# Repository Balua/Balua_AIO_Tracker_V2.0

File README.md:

### Balua_AIO_Tracker_V2.0 - Board finished for printing, schematic and layout completed but still to be tested...

#### Updated version of the original tracker found in the Balua_AIO_Tracker_V1.0 repository with extra features and small corrections

#### Features:

#####Microprocessor
- ATMEGA 328p smd package

#####Power
- Step up Boost Converters from 2 AA Batteries to 3.3V and 5V

#####Communication
- Radiometrix HX1 - VHF Narrow Band FM High Power (300mW) Transmitter with SMA Antenna
- RFM22B ISM Transceiver Module with SMA Antenna

#####GPS
- Ublox Max 7 GPS with Quad V GPS antenna with jumpers in the RX/TX line and in the I2C for hardware selectable communication mode (NEW!!!)

#####Sensors
- SMD Onewire temperature sensor - DS18B20
- Battery Voltage sensing
- 0-15psi Pressure Sensor SMT mount - HSCSANN015PA2A3
- 9-axis Motion Tracking MEMS (3-axis gyroscope, 3-axis accelerometer and magnetometer) - MPU-9150 (NEW!!!)

#####Storage
- MicroSD Socket

#####Programming
- SMD AVR SPI Programming pins available (NEW!!!)

#####External pins
- I2c Pins with pull-up for expansion available
- 2 pins for Software Serial
- 2 pins for Hardware Serial
- Power Pins for external power (VBatt, 5V, 3.3V and GND) (NEW!!!)
- Power pins for Cutoff system (NEW!!!)

#####Other
- On Board AA battery holder
- 5V boost converter with enable controllable
- UBlox GPS Power ON Controllable
- RFM22B Radio enable pin Controllable
- On board LED
- Cutoff System implemented (NEW!!!)

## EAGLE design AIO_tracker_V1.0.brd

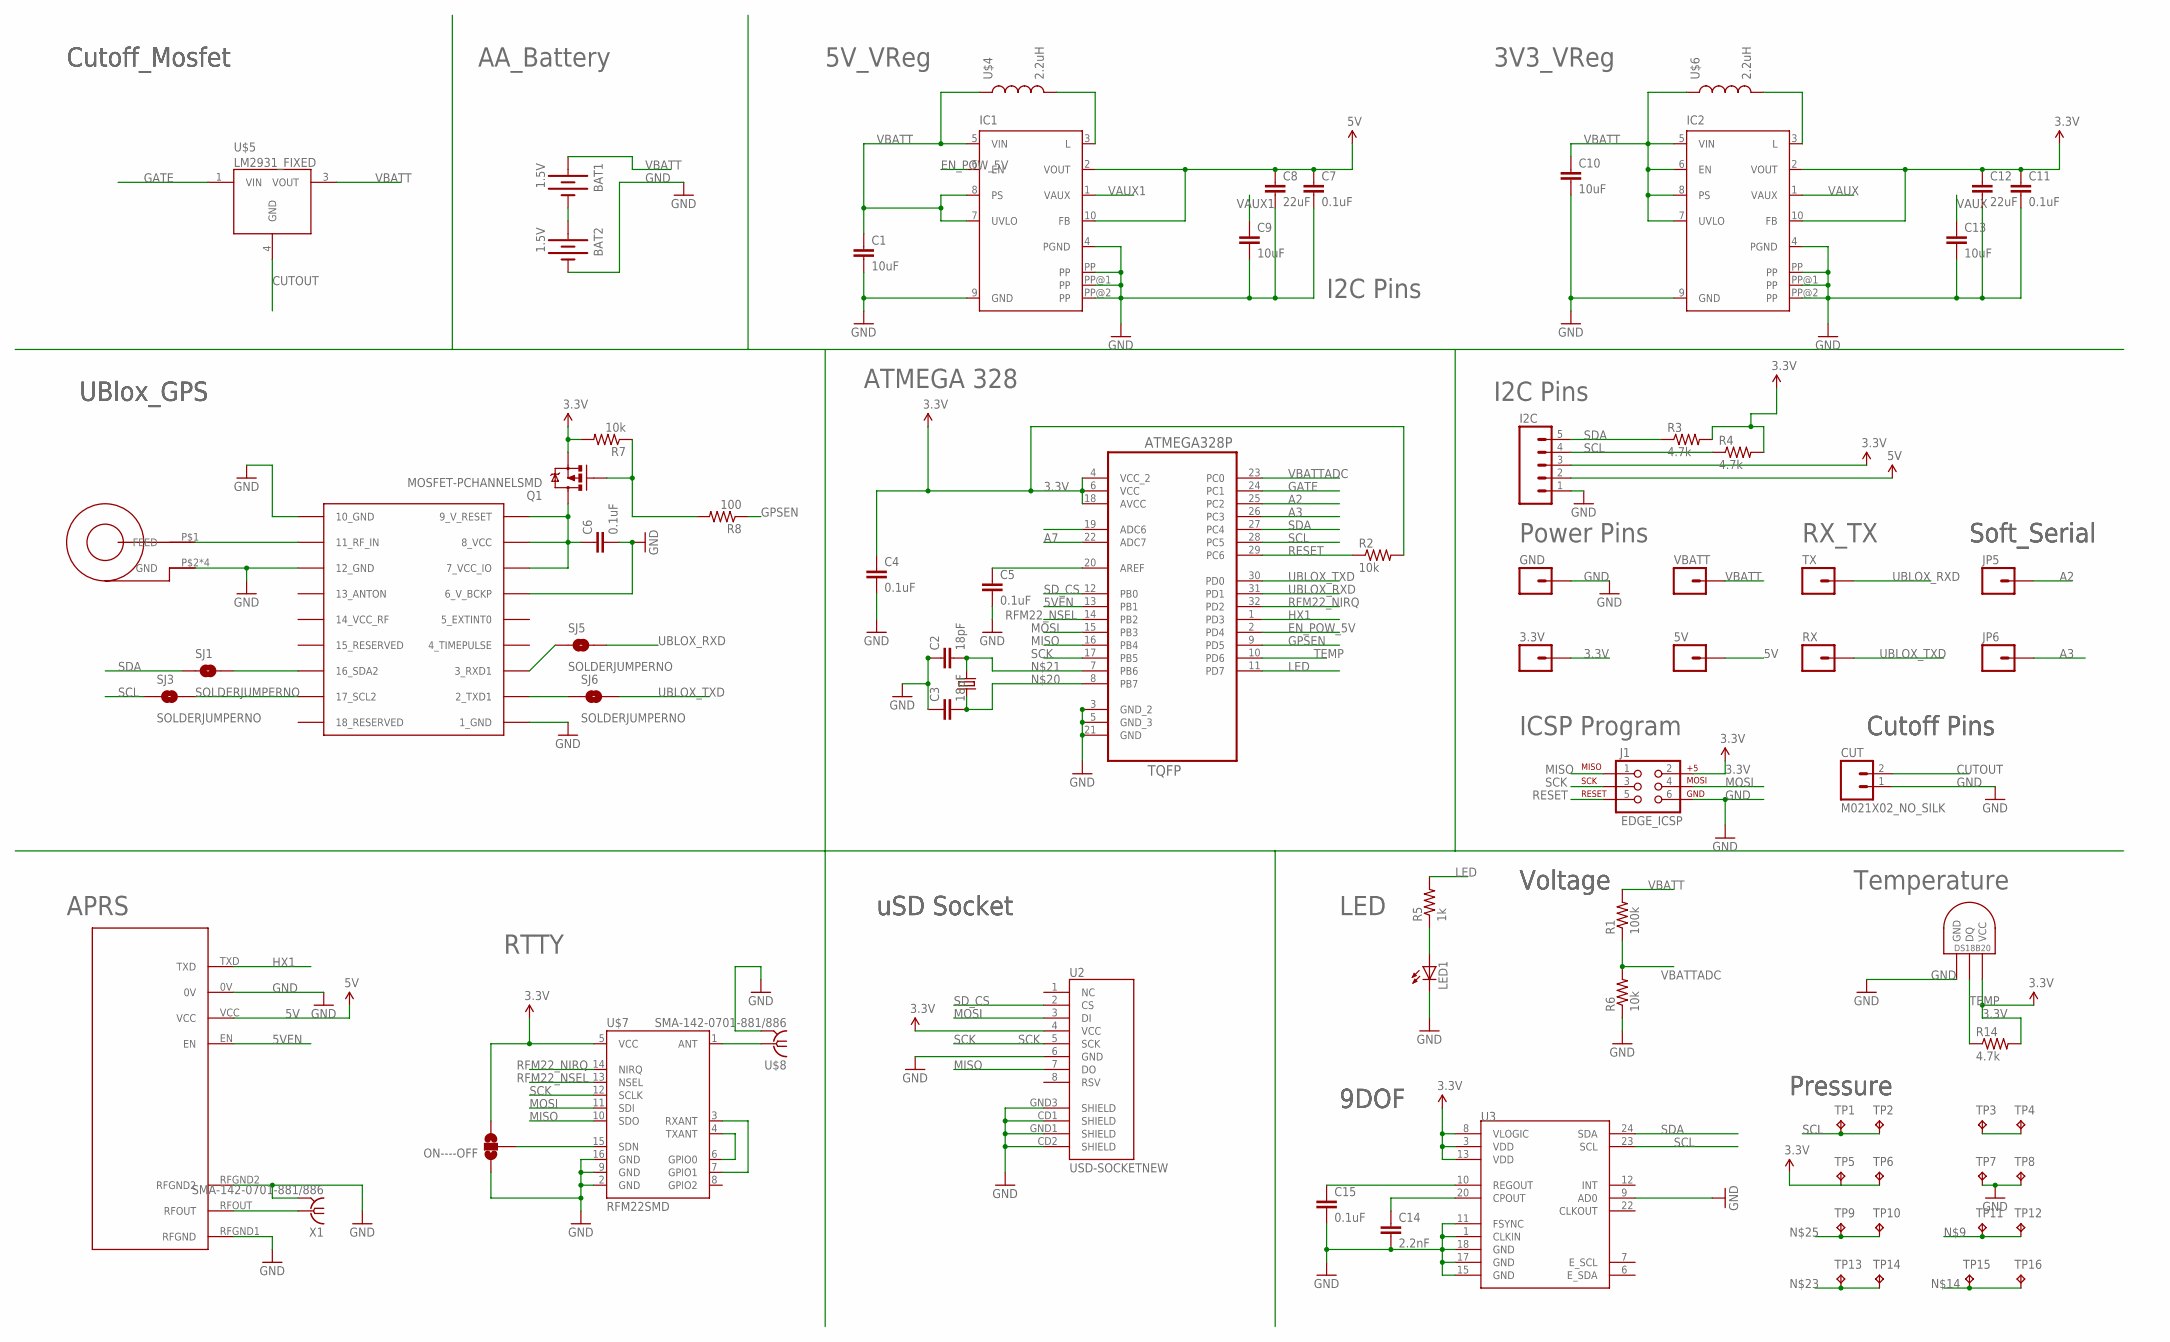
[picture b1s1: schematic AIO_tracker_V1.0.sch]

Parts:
3.3V, 5V: M01SMDNS; 1X01NS
BAT1, BAT2: 1.5V; BATTERY-AA-KIT
C1, C9, C10, C13: 10uF; 0805
C2, C3: 18pF; 0603-CAP
C4, C5, C6, C7, C11, C15: 0.1uF; 0603-CAP
C8, C12: 22uF; 0805
C14: 2.2nF; 0603-CAP
CUT: M021X02_NO_SILK; 1X02_NO_SILK
GND: M01SMDNS; 1X01NS
I2C: M05NO_SILK; 1X05_NO_SILK
IC1, IC2: TPS61201; S-PDSO-N10
J1: EDGE_ICSP; EDGE_MOUNTED_ICSP
JP5, JP6: M01PTH; 1X01
LED1: LED0603; LED-0603
ON----OFF: SOLDERJUMPER_2WAY-OLDT; SJ_2
Q1: MOSFET-PCHANNELSMD; SOT23-3
R1: 100k; 0603-RES
R2, R6, R7: 10k; 0603-RES
R3, R4, R14: 4.7k; 0603-RES
R5: 1k; 0603-RES
R8: 100; 0603-RES
RX: M01PTH; 1X01
SJ1, SJ3, SJ5, SJ6: SOLDERJUMPERNO; SJ_2S-NO
TP1, TP2, TP3, TP4, TP5, TP6, TP7, TP8, TP9, TP10, TP11, TP12, TP13, TP14, TP15, TP16: TPTP10SQ; TP10SQ
TX: M01PTH; 1X01
U1: ATMEGA328P-AU; QFP80P900X900X120-32N
U2: USD-SOCKETNEW; MICRO-SD-SOCKET-PP
U3: MPU-9150QFN-24-NP; QFN-24-NP
U$1: UBLOX_MAX
U$2: JDGA-REMQV-ANTENNA; JDGA-RIGID_COMBO_PAD
U$3: NTX2-VERTICAL
U$4, U$6: 2.2uH; COILCRAFT_MSS5131
U$5: LM2931_FIXED; DPAK
U$7: RFM22SMD; RFM22-XXX-S2
U$8: SMA-142-0701-881/886; J502-ND-142-0701-881/886
U$9: DS1820; µSOP8
VBATT: M01SMDNS; 1X01NS
X1: SMA-142-0701-881/886; J502-ND-142-0701-881/886
Y1: ABRACON_ABM3_CRYSTAL

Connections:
3.3V: 3.3V.1, C4.1, C11.1, C12.1, I2C.3, IC2.2 (VOUT), IC2.10 (FB), J1.2, ON----OFF.3, Q1.2 (S), R2.2, R3.2, R4.2, R7.2, R14.2, TP5.TP, TP6.TP, U1.4 (VCC_2), U1.6 (VCC), U1.18 (AVCC), U2.4 (VCC), U3.3 (VDD), U3.8 (VLOGIC), U3.13 (VDD), U$7.5 (VCC), U$9.8 (VCC)
5V: 5V.1, C7.1, C8.1, I2C.2, IC1.2 (VOUT), IC1.10 (FB), U$3.VCC
5VEN: U1.13 (PB1), U$3.EN
A2: JP5.1, U1.25 (PC2)
A3: JP6.1, U1.26 (PC3)
A7: U1.22 (ADC7)
CUTOUT: CUT.2, U$5.4 (GND)
EN_POW_5V: IC1.6 (EN), U1.2 (PD4)
GATE: U1.24 (PC1), U$5.1 (VIN)
GND: BAT2.GND@1 (-), C1.2, C2.1, C3.1, C4.2, C5.2, C6.2, C7.2, C8.2, C9.2, C10.2, C11.2, C12.2, C13.2, C14.2, C15.2, CUT.1, GND.1, I2C.1, IC1.4 (PGND), IC1.9 (GND), IC1.PP, IC1.PP@1 (PP), IC1.PP@2 (PP), IC2.4 (PGND), IC2.9 (GND), IC2.PP, IC2.PP@1 (PP), IC2.PP@2 (PP), J1.6, LED1.C, ON----OFF.1, R6.1, TP7.TP, TP8.TP, U1.3 (GND_2), U1.5 (GND_3), U1.21 (GND), U2.6 (GND), U2.CD1 (SHIELD), U2.CD2 (SHIELD), U2.GND1 (SHIELD), U2.GND3 (SHIELD), U3.1 (CLKIN), U3.9 (AD0), U3.11 (FSYNC), U3.15 (GND), U3.17 (GND), U3.18 (GND), U$1.1_GND, U$1.6_V_BCKP, U$1.10_GND, U$1.12_GND, U$2.P$2 (GND), U$2.P$3 (GND), U$2.P$4 (GND), U$2.P$5 (GND), U$3.0V, U$3.RFGND1 (RFGND), U$3.RFGND2, U$7.2 (GND), U$7.9 (GND), U$7.16 (GND), U$8.G@1 (2), U$8.G@2 (2), U$8.G@3 (2), U$8.G@4 (2), U$9.4 (GND), X1.G@1 (2), X1.G@2 (2), X1.G@3 (2), X1.G@4 (2)
GPSEN: R8.1, U1.9 (PD5)
HX1: U1.1 (PD3), U$3.TXD
LED: R5.2, U1.11 (PD7)
MISO: J1.1, U1.16 (PB4), U2.7 (DO), U$7.10 (SDO)
MOSI: J1.4, U1.15 (PB3), U2.3 (DI), U$7.11 (SDI)
unnamed: LED1.A, R5.1
unnamed: Q1.1 (G), R7.1, R8.2
unnamed: U$1.11_RF_IN, U$2.P$1 (FEED)
unnamed: C5.1, U1.20 (AREF)
unnamed: U$3.RFOUT, X1.1
unnamed: C6.1, Q1.3 (D), U$1.7_VCC_IO, U$1.8_VCC, U$1.9_V_RESET
unnamed: IC1.3 (L), U$4.P$1 (2)
unnamed: TP11.TP, TP12.TP
unnamed: BAT1.GND@1 (-), BAT2.PWR@1 (+)
unnamed: SJ5.1, U$1.3_RXD1
unnamed: SJ6.1, U$1.2_TXD1
unnamed: U$7.1 (ANT), U$8.1
unnamed: TP15.TP, TP16.TP
unnamed: SJ1.2, U$1.16_SDA2
unnamed: SJ3.2, U$1.17_SCL2
unnamed: C15.1, U3.10 (REGOUT)
unnamed: C14.1, U3.20 (CPOUT)
unnamed: IC2.3 (L), U$6.P$1 (2)
unnamed: C3.2, U1.8 (PB7), Y1.P$1 (1)
unnamed: C2.2, U1.7 (PB6), Y1.P$2 (2)
unnamed: TP13.TP, TP14.TP
unnamed: TP9.TP, TP10.TP
unnamed: ON----OFF.2, U$7.15 (SDN)
unnamed: U$7.3 (RXANT), U$7.7 (GPIO1)
unnamed: U$7.4 (TXANT), U$7.6 (GPIO0)
RESET: J1.5, R2.1, U1.29 (PC6)
RFM22_NIRQ: U1.32 (PD2), U$7.14 (NIRQ)
RFM22_NSEL: U1.14 (PB2), U$7.13 (NSEL)
SCK: J1.3, U1.17 (PB5), U2.5 (SCK), U$7.12 (SCLK)
SCL: I2C.4, R4.1, SJ3.1, TP1.TP, TP2.TP, U1.28 (PC5), U3.23 (SCL)
SDA: I2C.5, R3.1, SJ1.1, TP3.TP, TP4.TP, U1.27 (PC4), U3.24 (SDA)
SD_CS: U1.12 (PB0), U2.2 (CS)
TEMP: R14.1, U1.10 (PD6), U$9.1 (DQ)
UBLOX_RXD: SJ5.2, TX.1, U1.31 (PD1)
UBLOX_TXD: RX.1, SJ6.2, U1.30 (PD0)
VAUX: C13.1, IC2.1 (VAUX)
VAUX1: C9.1, IC1.1 (VAUX)
VBATT: BAT1.PWR@1 (+), C1.1, C10.1, IC1.5 (VIN), IC1.7 (UVLO), IC1.8 (PS), IC2.5 (VIN), IC2.6 (EN), IC2.7 (UVLO), IC2.8 (PS), R1.2, U$4.P$2 (1), U$5.3 (VOUT), U$6.P$2 (1), VBATT.1
VBATTADC: R1.1, R6.2, U1.23 (PC0)

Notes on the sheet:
I2C Pins
Soft_Serial
RX_TX
Power Pins
ICSP Program
Cutoff Pins
5V_VReg
3V3_VReg
AA_Battery
Cutoff_Mosfet
UBlox_GPS
ATMEGA 328
uSD Socket
APRS
RTTY
LED
Voltage
9DOF
Pressure
Temperature

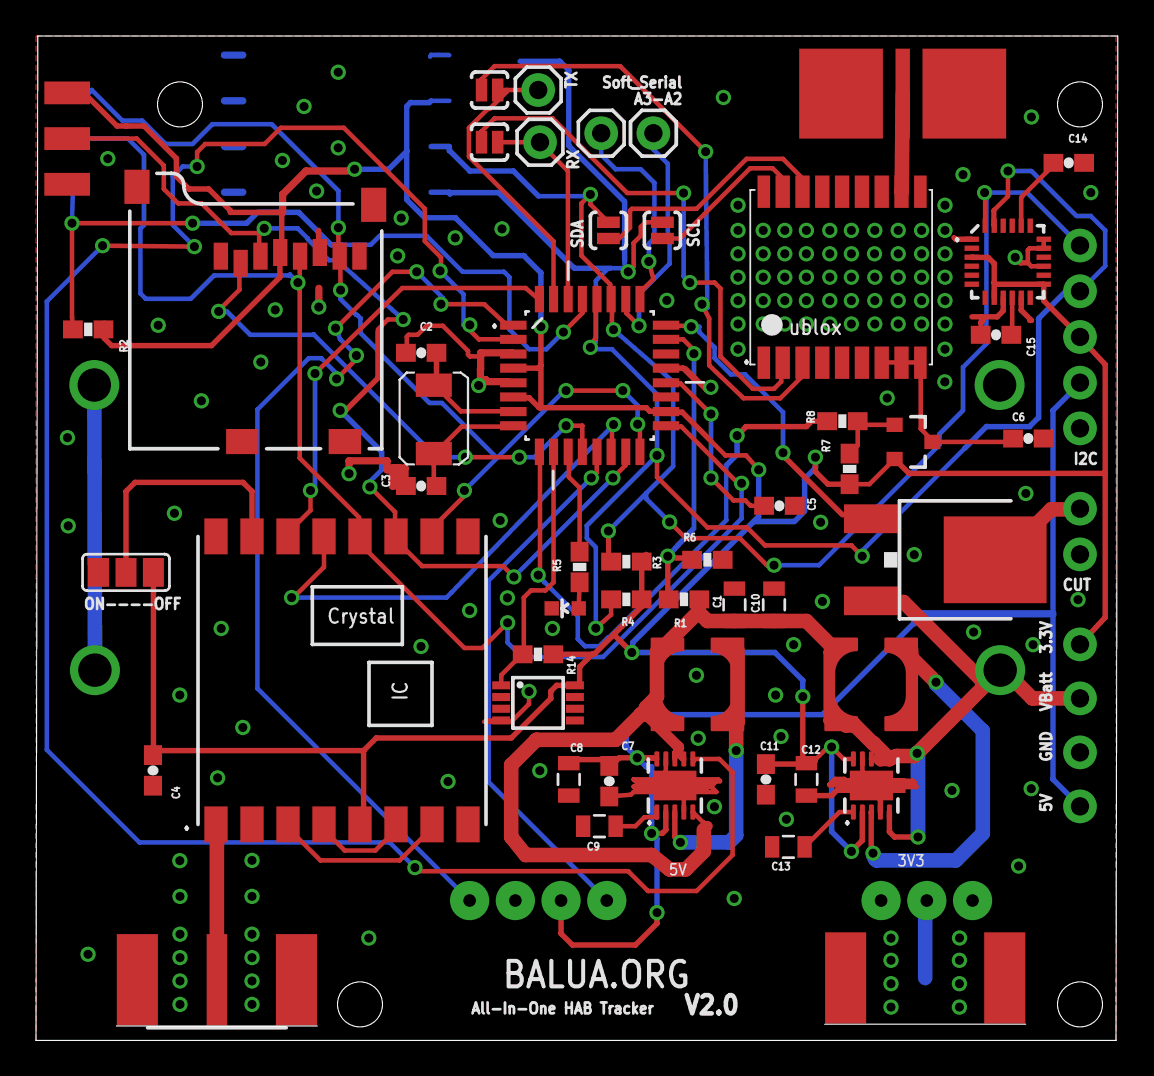
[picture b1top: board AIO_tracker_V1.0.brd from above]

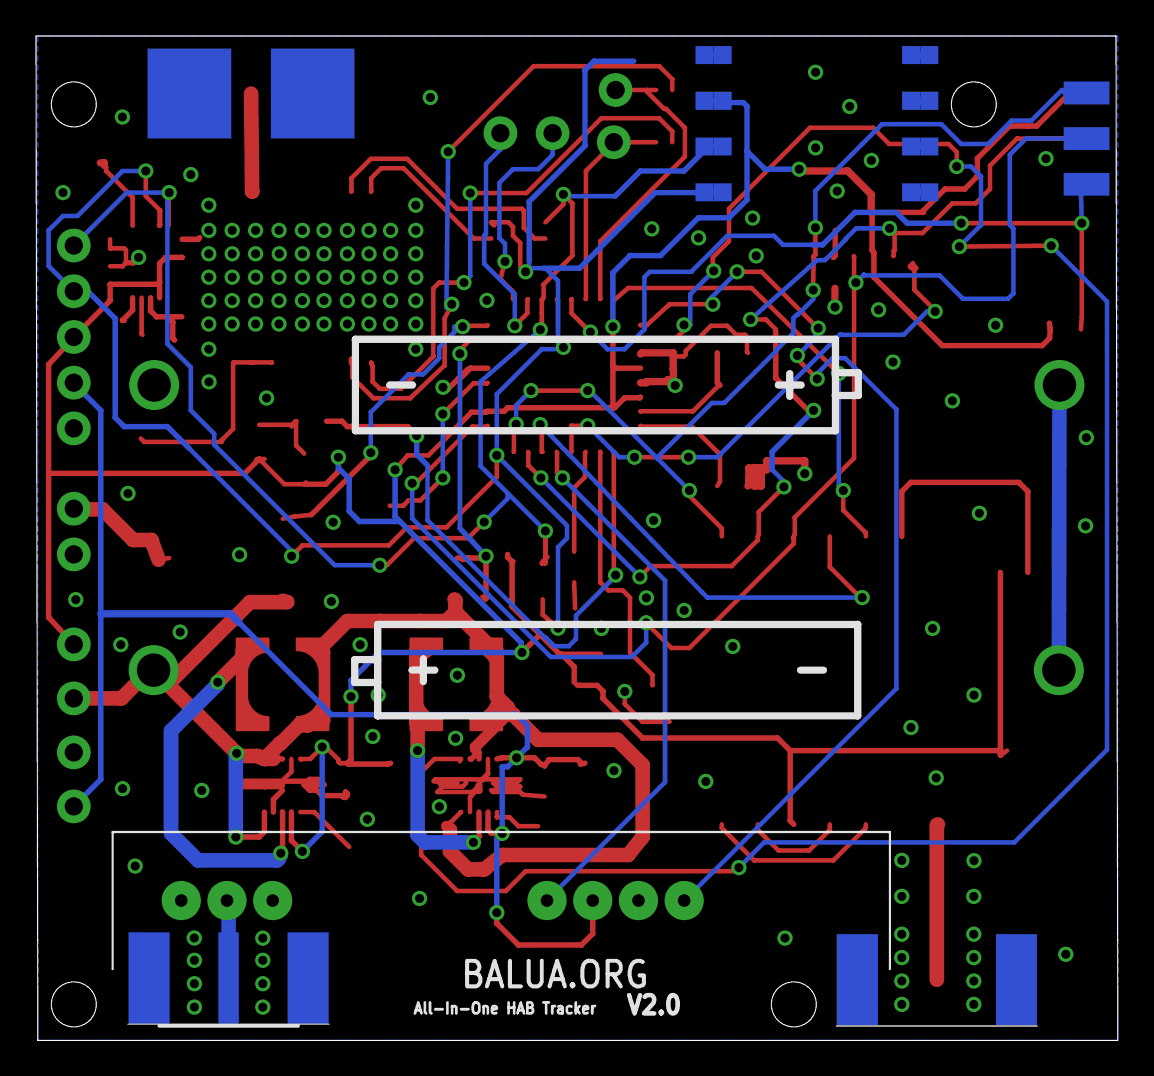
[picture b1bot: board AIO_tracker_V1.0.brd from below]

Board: 2 copper layers, 60.1 x 55.8 mm, 76 parts (20 on the bottom side), 53 nets.

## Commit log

2014-06-30 First Commit
    Main features implemented. Schematic and layout complete with minor
    changes that will be corrected in later commits
2014-06-30 Replaced tx pin of HX1 from PD4 to PD3
    Replaced tx pin of HX1 from PD4 to PD3 in atmega 328 and 5V enable from
    PD3 to PD4 due to the fact that the PD3 pin is a PWM pin
2014-06-30 Replaced 0306 smd caps with 0805 smd caps
    Replaced the package of the 0306 smd caps with 0805 smd caps of the
    larger capacitors (>10uF)
2014-06-30 Replaced HX1 Enable, added Soft Serial (A3 and A2)
    Replaced HX1 Enable with a non pwm pin, added soft serial (A2 and A3)
    silkscreened isolated pins.
2014-06-30 Added extra power pins (5V, 3.3V and GND) and more
    Added extra power pins (5V, 3.3V and GND)
    Added I2C to Ublox
    Placed smd jumpers in both I2C and RX/TX of Ublox for hardware selection
    of communication mode.
    Added pins for external RX/TX communication with arduino.
    PCB layout updated
2014-07-01 tirei o ponto final
    so para testar
2014-07-18 Updated library and erros
    - Ava library updated
    - SDN pin of the RFM22b connected to A6 instead of always HIGH
    - Updated Sarantel Antenna Footprint
    - A7 to external pin
2014-07-18 Updated read me
    Updated read me
2014-07-28 Added NTX2 Support option
    Added NTX2 Support option and finished routing
2014-07-28 corrected a few erros with the NTX2
    Added back pads to the HX1 footprint, corrected the voltage divider,
    corrected the antenna layout, changed SDN of RFM22b to the A7, corrected
    the values in the schematic
    Missing:
    - Cuttof system
    - New pressure sensor
2014-07-29 changed holes to match the stencil
    changed holes to match the stencil sticks (2.5mm) and the 10mm spacing
    between them
2014-08-04 removed jumpers and ntx2 support
    removed jumpers and ntx2 support
2014-08-05 added 9dof, new antena, new crystal, cutoff...
    added 9dof, new antena, new crystal, cutoff system and changed layout
2014-08-06 size and placement defined
2014-08-07 tracker routed
    tracker routed, some adjustments still in progress
2014-08-10 final but without logo
2014-08-10 Final without logo
2014-08-10 corrected pcb errors for oshpark
2014-08-10 corrected last things
2014-08-10 Small .sch changes
2014-08-10 final commit of pcb (fingers crossed)
2014-08-11 Several thing corrected (still....=/)
    Position of 9DOF, tended vias, names, etc
2014-08-11 last one seriously
2014-08-19 Added stencil top and bottom
    Added stencil top and bottom
2014-09-19 added dxf stencil top and bottom
2014-10-31 fixed some details after receiving the printed pcb
    - Fixed size of silkscreen
    - Added pin 1 points in silkscreen
    - Removed A6 and replaced the SDN of RFM22 with a 3way jumper
    Still need to be fixed
    - Pressure sensor size in pcb
    - Buy the correct SMA Jacks (
2014-10-31 added image of the PCB received from oshpark
2014-11-04 last changes post fabrication
    - changed position of the pressure sensor pins (reversed)
    - Added more spacing from the AA battery holders

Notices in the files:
parts and their libraries:
SparkFun-Passives: Licensing: CC v3.0 Share-Alike You are welcome to use this library for commercial purposes.
